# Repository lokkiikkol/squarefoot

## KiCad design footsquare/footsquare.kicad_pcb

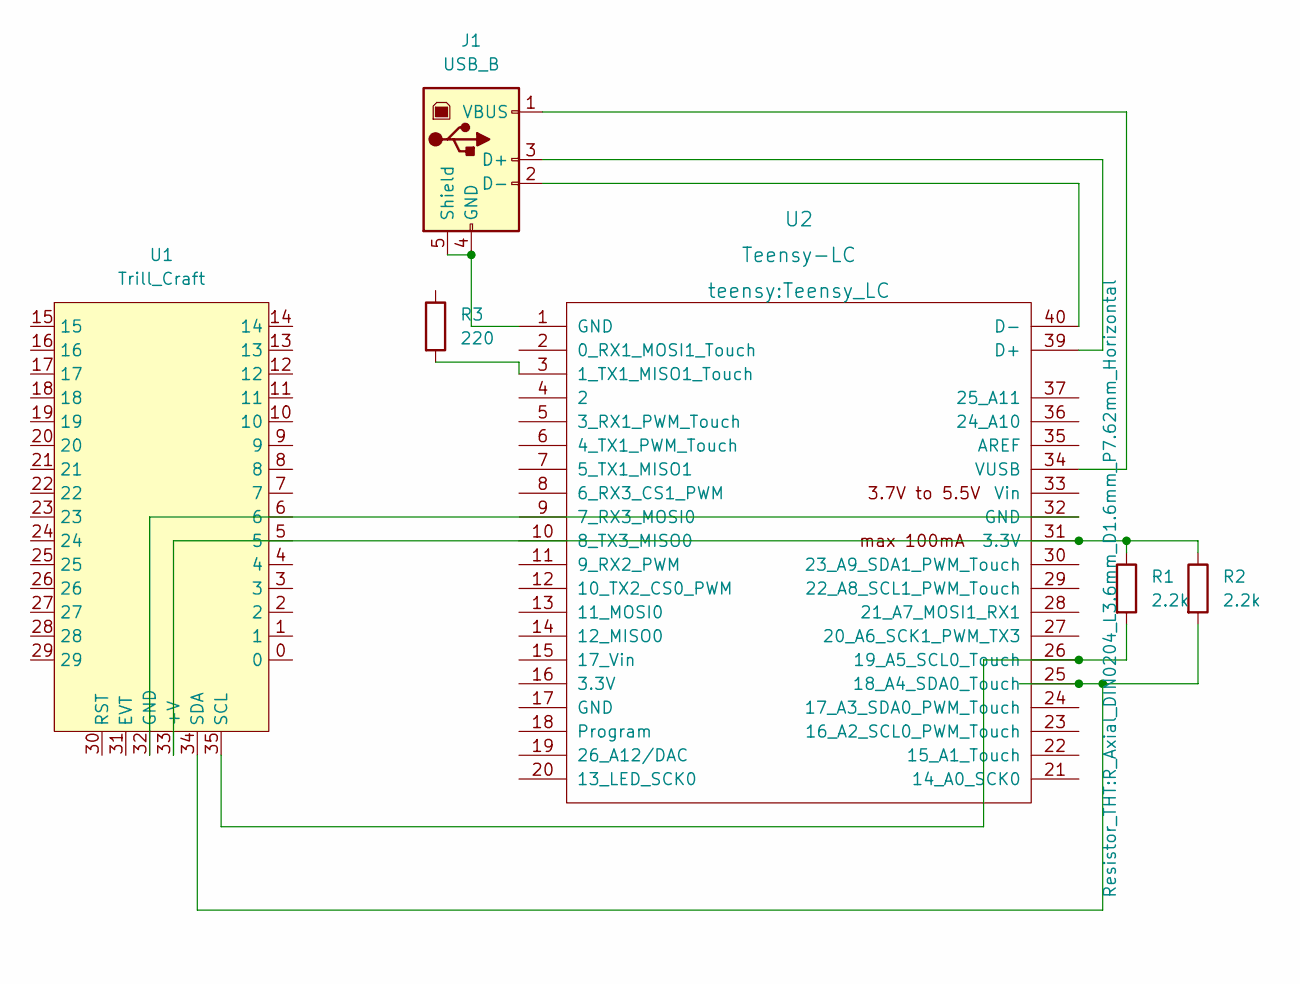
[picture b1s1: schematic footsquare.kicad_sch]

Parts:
J1: USB_B; USB_B_Lumberg_2411_02_Horizontal
R1, R2: 2.2k; R_Axial_DIN0204_L3.6mm_D1.6mm_P7.62mm_Horizontal
R3: 220; R_Axial_DIN0204_L3.6mm_D1.6mm_P7.62mm_Horizontal
U1: Trill_Craft
U2: Teensy-LC; Teensy_LC

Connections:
unnamed: J1.1 (VBUS), U2.34 (VUSB)
unnamed: J1.2 (D-), U2.40 (D-)
unnamed: J1.3 (D+), U2.39 (D+)
unnamed: J1.4 (GND), J1.5 (Shield), U2.1 (GND)
unnamed: R1.1, R2.1, U1.33 (+V), U2.31 (3.3V)
unnamed: R1.2, U1.35 (SCL), U2.26 (19_A5_SCL0_Touch)
unnamed: R2.2, U1.34 (SDA), U2.25 (18_A4_SDA0_Touch)
unnamed: U1.32 (GND), U2.32 (GND)
unnamed: R3.2, U2.3 (1_TX1_MISO1_Touch)

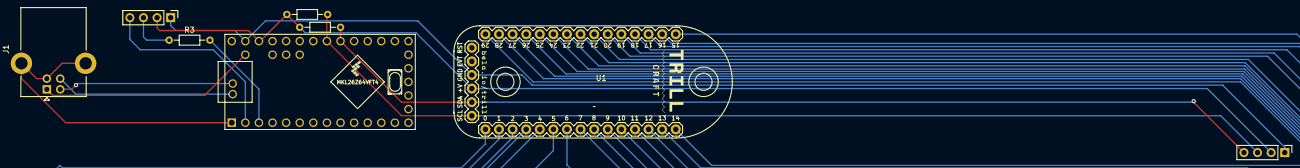
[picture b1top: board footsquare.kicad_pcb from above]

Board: 2 copper layers, 6 parts (0 on the bottom side), 9 nets.

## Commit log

2022-07-19 initial upload, first pcb version
2022-07-19 new version with encoder and ground plane
    -ground plane added
    -encoder added
    -outline added
